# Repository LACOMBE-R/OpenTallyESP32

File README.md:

# OpenTallyESP32

A wireless tally light system built around the **Seeed XIAO ESP32-C3**. Each unit connects to a WebSocket tally server over Wi-Fi and lights up its two NeoPixel LEDs to show the live camera state (Program / Preview / Idle). Battery level is reported to the server automatically.

This project was created for the [orKs](https://lce.gg/) association for the **LCE** ([lce.gg](https://lce.gg/)) event, to manage camera tally signaling during live productions.

---

## Hardware

| Component | Details |
|-----------|---------|
| MCU | Seeed Studio XIAO ESP32-C3 |
| LEDs | 3× NeoPixel (WS2812B), pin **D8** — 2 rear + 1 front-facing |
| Button | Tactile switch, pin **D1** (GPIO 3) |
| Battery sensing | Enable pin **D0**, ADC pin **D2** — voltage divider, 3.0 V–4.2 V range |

The KiCad schematic and PCB layout are in [`ECAD/OpenTallyESP32/`](ECAD/OpenTallyESP32/).

---

## Firmware

### Prerequisites

- [PlatformIO](https://platformio.org/) (VS Code extension or CLI)

### Credentials

Sensitive values (WiFi credentials, WebSocket server) are kept out of version control in a local file:

```
Firmware/OpenTallyESP32/include/credentials.h
```

This file is listed in `.gitignore` and will never be committed. Before building, copy the example file and fill in your values:

```bash
cp include/credentials.h.example include/credentials.h
```

```cpp
#define DEFAULT_WIFI_SSID  "your_ssid"
#define DEFAULT_WIFI_PASS  "your_password"
#define DEFAULT_WS_HOST    "your.websocket.server"
#define DEFAULT_WS_PORT    80
```

These defines are used as fallback defaults when no configuration has been saved to flash yet. Once configured via the dashboard, the flash values take over and these defaults are no longer used.

### Dependencies (resolved automatically by PlatformIO)

- `adafruit/Adafruit NeoPixel`
- `links2004/WebSockets`
- `bblanchon/ArduinoJson`

---

## Configuration

### NVS flash storage

Configuration is persisted in the ESP32's **NVS (Non-Volatile Storage)** — a key-value store built into the flash that survives resets and power cuts. The Arduino `Preferences` library is used to read and write it under the namespace `opentally`.

Values are written only when the user submits the config form; they are read once at every boot before anything else runs. If a key has never been written, the firmware falls back to the compiled-in default shown below.

| Key | Type | Default | Description |
|-----|------|---------|-------------|
| `camera_id` | string | `cam01` | Camera identifier sent in every WebSocket message |
| `ws_host` | string | `your.websocket.server` | WebSocket server hostname |
| `ws_port` | uint16 | `80` | WebSocket server port |
| `wifi_ssid` | string | — | Wi-Fi network name |
| `wifi_pass` | string | — | Wi-Fi password |

### Entering configuration mode

Hold the button for **5 seconds** at power-on (or after waking from deep sleep). The LEDs will turn **solid purple** to confirm the long-press was detected.

The device starts a Wi-Fi access point:

- **SSID:** `OpenTally-Config`
- **Password:** `opentally`

Connect to it and open **http://192.168.4.1** in a browser. Fill in the form and click *Configurer*. The device saves the settings to NVS, confirms with a countdown banner, then restarts into normal mode.

### Operating modes — flowchart

```
                        ┌─────────────────┐
                        │   Power on /    │
                        │  Wake from deep │
                        │      sleep      │
                        └────────┬────────┘
                                 │
                        Load NVS config
                                 │
                    ┌────────────▼────────────┐
                    │  Button held on boot?   │
                    └────┬──────────────┬─────┘
                  Yes ≥5s│              │No
                         │              │
           ┌─────────────▼──┐    ┌──────▼───────────────┐
           │   AP / Config  │    │     Normal mode      │
           │     mode       │    │  Connect to Wi-Fi    │
           │ SSID: OpenTally│    └─────┬────────────────┘
           │ IP: 192.168.4.1│          │
           │ LEDs: purple   │    ┌─────▼─────────────────────┐
           │   blink        │    │  Wi-Fi connected in 30s?  │
           └─────────┬──────┘    └──┬─────────────────────┬──┘
                     │           No │                     │ Yes
              Serve config    ┌─────▼──────┐    ┌─────────▼──────────┐
                  form        │ Deep sleep │    │  Connect WebSocket │
                     │        └────────────┘    └─────────┬──────────┘
              User submits                                │
                     │                       ┌────────────▼───────────┐
              Save to NVS                    │      Main loop         │
                     │                       │  ┌──────────────────┐  │
                  Restart                    │  │ WS msg received  │  │
                                             │  │  → update LEDs   │  │
                                             │  │    RED / GREEN / │  │
                                             │  │      OFF         │  │
                                             │  └──────────────────┘  │
                                             │  ┌──────────────────┐  │
                                             │  │ Every 30s        │  │
                                             │  │ → send battery % │  │
                                             │  └──────────────────┘  │
                                             │  ┌──────────────────┐  │
                                             │  │ Button press     │  │
                                             │  │  → deep sleep    │  │
                                             │  └──────────────────┘  │
                                             └────────────────────────┘
```

---

## Operation

### Boot sequence

1. Device loads saved configuration from NVS.
2. If button is held ≥ 5 s → **AP / config mode** (see above).
3. Otherwise → **normal mode**: connects to the configured Wi-Fi.

### LED states

The device has two **rear LEDs** (visible to the operator) and one **front LED** (visible to the talent, facing the subject).

**Tally states**

| State | Rear LEDs (0 & 1) | Front LED (2) |
|-------|-------------------|---------------|
| Program (on air) | Red | Red |
| Preview | Green | Off |
| Program + Preview | Red (program takes priority) | Red |
| Idle | Off | Off |

**Status patterns**

Slow-blink patterns affect rear LEDs only (front LED stays off). Quick-flash patterns fill all 3 LEDs.

| Color | Pattern | Front LED | Meaning |
|-------|---------|-----------|---------|
| Blue | Slow blink | Off | Connecting to Wi-Fi |
| Green | 5 quick flashes | On | Wi-Fi connected |
| Red | Slow blink | Off | WebSocket disconnected |
| Purple | Slow blink | Off | AP config mode active |
| Red | 3 quick flashes | On | Entering deep sleep |

### Power saving

- After Wi-Fi connects the CPU is throttled to **80 MHz** and Wi-Fi modem-sleep is enabled.
- Press the button at any time — including during Wi-Fi connection — to immediately enter **deep sleep**. The device will wake again on the next button press.
- If Wi-Fi does not connect within **30 seconds**, the device goes to deep sleep automatically.

### Battery reporting

On WebSocket connection, and every **30 seconds** thereafter, the device reads the battery voltage and sends the percentage to the tally server (only if the value changed). The server can display it in any connected control surface.

---

## WebSocket protocol

> **Note:** The WebSocket backend used at LCE is not open source. It pulls live camera states directly from a **Blackmagic ATEM** video switcher and broadcasts them to all connected tally units. However, the protocol is straightforward enough to reimplement — any server that speaks the JSON messages below can drive these tally units.

All messages are JSON objects with at least an `action` field and, where relevant, a `camera` field and a `content` object.

### Messages sent by the tally unit (firmware)

| Action | Extra fields | Description |
|--------|-------------|-------------|
| `SubscribeCamera` | `camera` | Subscribe to state updates for the given camera ID. The server will push updates whenever the camera's program/preview state changes. |
| `GetCameraProperties` | `camera` | Request the current program/preview state of a camera immediately after connecting. |
| `SetBatteryLevel` | `camera`, `content.batteryLevel` (integer 0–100) | Report the tally unit's battery percentage to the server. Sent on connection, then every 30 s if the value changed. |

### Messages sent by the browser controller (`tally-control.html`)

| Action | Extra fields | Description |
|--------|-------------|-------------|
| `ActAsSender` | — | Identifies this client as a control surface (sender), not a passive tally receiver. |
| `SubscribeCamera` | `camera` | Subscribe to state updates for a camera (same as firmware). |
| `GetCameraProperties` | `camera` | Request the current state immediately. |
| `SetCameraProperties` | `camera`, `content.program` (bool), `content.preview` (bool) | Set the tally state of a camera. Both fields must be present; at most one should be `true`. |

### Messages received from the server

| Trigger | Expected fields | Description |
|---------|----------------|-------------|
| State change or reply to `GetCameraProperties` | `content.program` (bool), `content.preview` (bool) | Pushed to all subscribers whenever a camera's state changes. The firmware and browser controller both read these two booleans to update their display. |

---

## Browser control tool

[`tally-control.html`](tally-control.html) is a standalone HTML file intended primarily for **testing purposes** — useful to verify the WebSocket server is working and to trigger tally states without needing physical hardware. Open it in any browser, enter the WebSocket URL (e.g. `ws://your.websocket.server:80/`) and the camera ID, then click **Connecter**. You can then manually set a camera to **Idle**, **Preview**, or **Program**. All messages sent and received are shown in the log panel.

---

## Repository structure

```
OpenTallyESP32/
├── ECAD/
│   ├── LIB/                  KiCad symbol and footprint library (XIAO ESP32-C3)
│   └── OpenTallyESP32/       KiCad project (schematic, PCB layout)
│       ├── *.kicad_*         KiCad project files
│       ├── *.gbr / *.gbrjob  Gerber files for PCB manufacturing
│       ├── *.dxf             DXF exports
│       └── OpenTallyESP32PCB.step  3D STEP model
├── Firmware/
│   └── OpenTallyESP32/
│       ├── src/main.cpp      Full firmware source
│       ├── include/          credentials.h.example (copy to credentials.h before building)
│       ├── test/             Manual test sketches
│       └── platformio.ini    PlatformIO project config
└── tally-control.html        Browser-based tally controller
```

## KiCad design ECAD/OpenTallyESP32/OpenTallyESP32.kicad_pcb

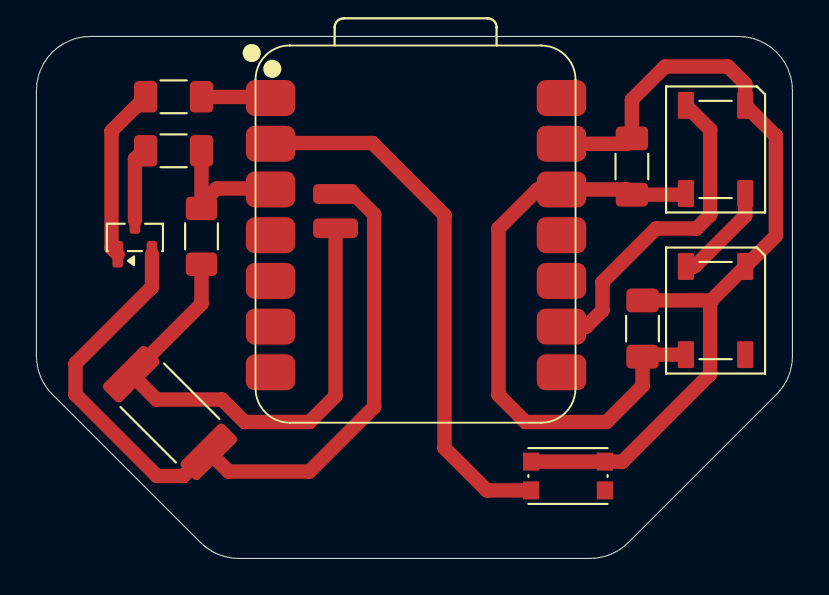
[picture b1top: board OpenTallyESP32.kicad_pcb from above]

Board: 2 copper layers, 42.0 x 29.0 mm, 11 parts (0 on the bottom side), 11 nets.

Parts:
C1, C2: C_Small; C_1206_3216Metric_Pad1.33x1.80mm_HandSolder
D1, D2: WS2812B; LED_WS2812B_PLCC4_5.0x5.0mm_P3.2mm
J1: Conn_01x02; R_2512_6332Metric_Pad1.40x3.35mm_HandSolder
Q1: AO3400A; SOT-23
R1, R2, R3: R_Small; R_1206_3216Metric_Pad1.30x1.75mm_HandSolder
SW1: SW_Push; SW_Push_1P1T_NO_CK_KMR2
U1: XIAO ESP32C3; XIAO-ESP32-C3-SMD

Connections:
+3.3V: C1.1, C2.1, D1.1 (VDD), D2.1 (VDD), U1.12 (VCC_3V3)
+BATT: J1.2, R1.1, U1.15 (Batt+)
-BATT: J1.1, Q1.2 (S), U1.16 (Batt-)
BATT_LEVEL: R1.2, R2.1, U1.3 (D2)
BATT_READ: R3.1, U1.1 (D0)
GND: C1.2, C2.2, D1.3 (VSS), D2.3 (VSS), SW1.2, U1.13 (GND)
NEOPIXEL: D2.4 (DIN), U1.9 (D8)
unnamed: D1.4 (DIN), D2.2 (DOUT)
unnamed: Q1.3 (D), R2.2
unnamed: Q1.1 (G), R3.2
SW: SW1.1, U1.2 (D1)

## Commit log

2026-03-15 Kicad project creation
2026-05-05 Added ESP32
2026-05-06 Jeff a terminé la chignole
2026-05-07 Added Firmware and HTML minimal controler
2026-05-07 Modified behavior and added battery level upstream
2026-05-07 PCB Save
2026-05-21 Added README.md
2026-05-21 Clarified README
2026-05-21 Fixed operating modes flowchart
2026-05-21 Fixed flowchart
2026-05-21 Fix flowchart arrow
2026-05-21 Moved battery solder pads and minor tweaks to routing
2026-05-26 Updated PCB for better integration and exported manufacturing files
2026-06-05 updated code to 3 WS2812 and created fab files for pcb
2026-06-06 Update configuration and documentation for 3 NeoPixels; add status LED functionality
2026-06-08 Add credentials management and update default values in documentation
2026-06-09 Update README with LED status patterns and add OpenTally guide PDF
